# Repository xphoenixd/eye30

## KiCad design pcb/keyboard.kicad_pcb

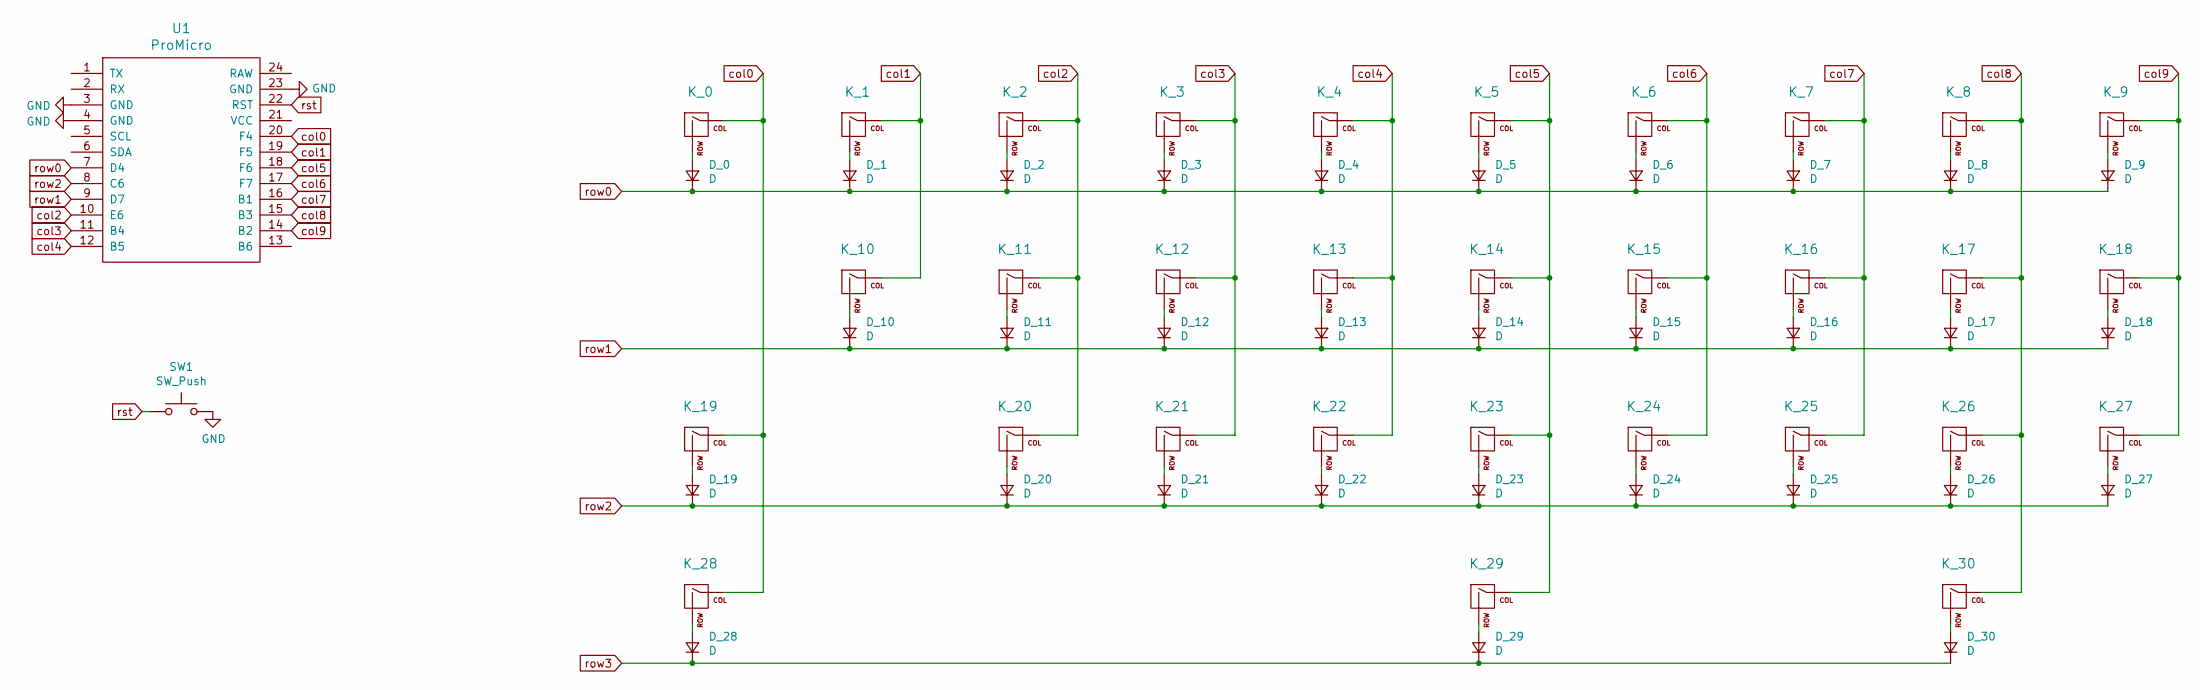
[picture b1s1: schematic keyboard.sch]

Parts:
D_0, D_1, D_2, D_3, D_4, D_5, D_6, D_7, D_8, D_9, D_10, D_11, D_12, D_13, D_14, D_15, D_16, D_17, D_18, D_19, D_20, D_21, D_22, D_23, D_24, D_25, D_26, D_27, D_28, D_29, D_30: D; D_SOD-123
K_0, K_1, K_2, K_3, K_4, K_5, K_6, K_7, K_8, K_9, K_10, K_11, K_12, K_13, K_14, K_15, K_16, K_17, K_18, K_20, K_21, K_22, K_23, K_24, K_25, K_26: KEYSW; MX-1U-NoLED
K_19, K_27: KEYSW; MX-1.25U-NoLED
K_28, K_30: KEYSW; MX-2.5U-NoLED
K_29: KEYSW; MX-5U-NoLED
SW1: SW_Push; SW_PUSH_6mm
U1: ProMicro

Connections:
GND: SW1.2, U1.3 (GND), U1.4 (GND), U1.23 (GND)
unnamed: D_0.2 (A), K_0.2 (ROW)
unnamed: D_1.2 (A), K_1.2 (ROW)
unnamed: D_2.2 (A), K_2.2 (ROW)
unnamed: D_3.2 (A), K_3.2 (ROW)
unnamed: D_4.2 (A), K_4.2 (ROW)
unnamed: D_5.2 (A), K_5.2 (ROW)
unnamed: D_6.2 (A), K_6.2 (ROW)
unnamed: D_7.2 (A), K_7.2 (ROW)
unnamed: D_8.2 (A), K_8.2 (ROW)
unnamed: D_9.2 (A), K_9.2 (ROW)
unnamed: D_10.2 (A), K_10.2 (ROW)
unnamed: D_11.2 (A), K_11.2 (ROW)
unnamed: D_12.2 (A), K_12.2 (ROW)
unnamed: D_13.2 (A), K_13.2 (ROW)
unnamed: D_14.2 (A), K_14.2 (ROW)
unnamed: D_15.2 (A), K_15.2 (ROW)
unnamed: D_16.2 (A), K_16.2 (ROW)
unnamed: D_17.2 (A), K_17.2 (ROW)
unnamed: D_18.2 (A), K_18.2 (ROW)
unnamed: D_19.2 (A), K_19.2 (ROW)
unnamed: D_20.2 (A), K_20.2 (ROW)
unnamed: D_21.2 (A), K_21.2 (ROW)
unnamed: D_22.2 (A), K_22.2 (ROW)
unnamed: D_23.2 (A), K_23.2 (ROW)
unnamed: D_24.2 (A), K_24.2 (ROW)
unnamed: D_25.2 (A), K_25.2 (ROW)
unnamed: D_26.2 (A), K_26.2 (ROW)
unnamed: D_27.2 (A), K_27.2 (ROW)
unnamed: D_28.2 (A), K_28.2 (ROW)
unnamed: D_29.2 (A), K_29.2 (ROW)
unnamed: D_30.2 (A), K_30.2 (ROW)
col0: K_0.1 (COL), K_19.1 (COL), K_28.1 (COL), U1.20 (F4)
col1: K_1.1 (COL), K_10.1 (COL), U1.19 (F5)
col2: K_2.1 (COL), K_11.1 (COL), K_20.1 (COL), U1.10 (E6)
col3: K_3.1 (COL), K_12.1 (COL), K_21.1 (COL), U1.11 (B4)
col4: K_4.1 (COL), K_13.1 (COL), K_22.1 (COL), U1.12 (B5)
col5: K_5.1 (COL), K_14.1 (COL), K_23.1 (COL), K_29.1 (COL), U1.18 (F6)
col6: K_6.1 (COL), K_15.1 (COL), K_24.1 (COL), U1.17 (F7)
col7: K_7.1 (COL), K_16.1 (COL), K_25.1 (COL), U1.16 (B1)
col8: K_8.1 (COL), K_17.1 (COL), K_26.1 (COL), K_30.1 (COL), U1.15 (B3)
col9: K_9.1 (COL), K_18.1 (COL), K_27.1 (COL), U1.14 (B2)
row0: D_0.1 (K), D_1.1 (K), D_2.1 (K), D_3.1 (K), D_4.1 (K), D_5.1 (K), D_6.1 (K), D_7.1 (K), D_8.1 (K), D_9.1 (K), U1.7 (D4)
row1: D_10.1 (K), D_11.1 (K), D_12.1 (K), D_13.1 (K), D_14.1 (K), D_15.1 (K), D_16.1 (K), D_17.1 (K), D_18.1 (K), U1.9 (D7)
row2: D_19.1 (K), D_20.1 (K), D_21.1 (K), D_22.1 (K), D_23.1 (K), D_24.1 (K), D_25.1 (K), D_26.1 (K), D_27.1 (K), U1.8 (C6)
row3: D_28.1 (K), D_29.1 (K), D_30.1 (K)
rst: SW1.1, U1.22 (RST)

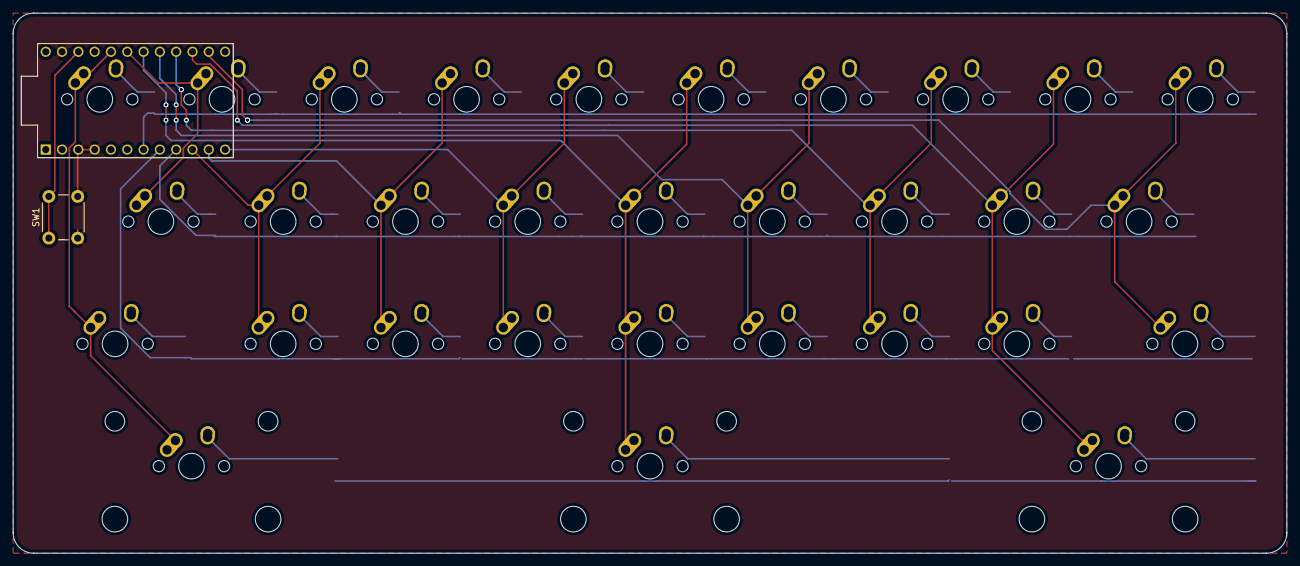
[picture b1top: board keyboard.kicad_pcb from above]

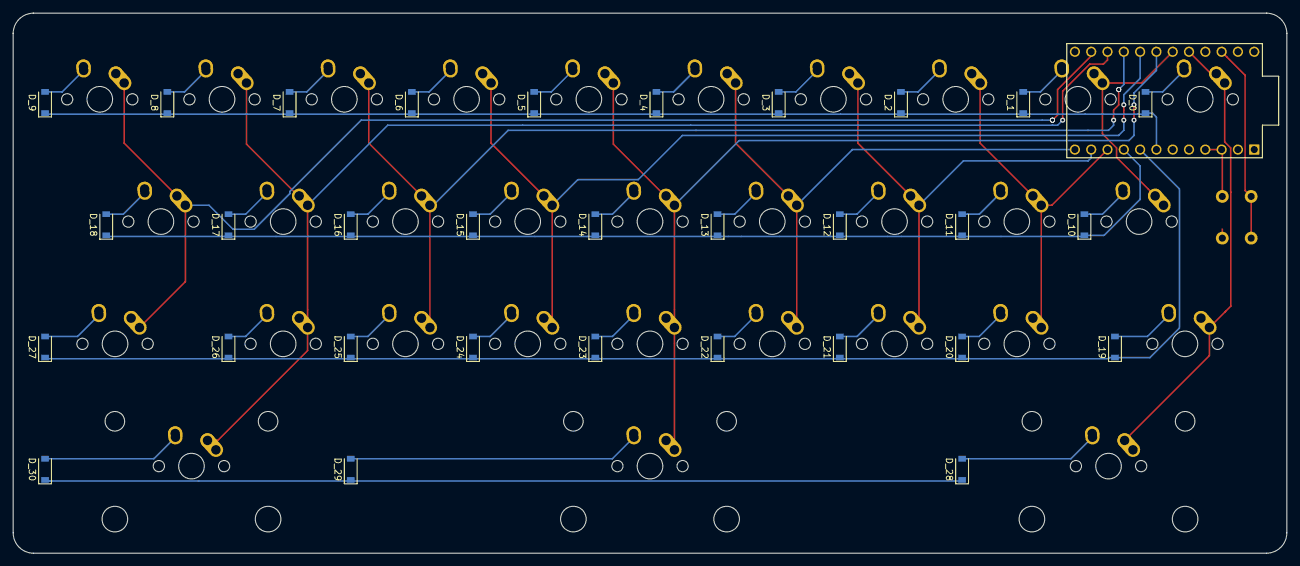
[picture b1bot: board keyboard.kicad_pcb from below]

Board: 2 copper layers, 198.4 x 84.1 mm, 64 parts (31 on the bottom side), 47 nets.

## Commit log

2021-07-14 First layout of the PCB done
2021-07-15 Fixed small errors and added a GND plane
